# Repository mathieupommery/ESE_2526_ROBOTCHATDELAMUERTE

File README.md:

# Cat-and-Mouse Robot Project

## Table of contents
1. [Introduction](#1-introduction)
2. [FOC omniwheel](#2-foc-omniwheel)
   1. [Hardware](#21-hardware)
      1. [Electronics](#211-electronics)
      2. [Mechanics](#212-mechanics)
   2. [Software (Overview)](#22-software-overview)
   3. [Bottleneck](#23-bottleneck)
3. [DC omniwheel](#3-dc-omniwheel)
   1. [New Motor control PCB](#31-new-motor-control-pcb)
   2. [Adapting the frame to allocate new DC motors, and more...](#32-adapting-the-frame-to-allocate-new-dc-motors-and-more)
   3. [Movement strategy](#33-movement-strategy)
      1. [Cat mode](#331-cat-mode)
      2. [Mouse mode](#332-mouse-mode)
   4. [Issues](#34-issues)
4. [Regular DC](#4-regular-dc)
   1. [Hardware](#41-hardware)
5. [Strategy Implementation](#5-strategy-implementation)
   1. [Overview of Cat/Mouse Mode](#51-overview-of-cat/mouse-mode)
   2. [LiDAR handling](#52-lidar-handling)
   3. [Motor control](#53-motor-control)
   4. [Additional PIMP mode](#54-additional-pimp-mode)

## 1. Introduction
This project aims to design and build a **mobile robotic system** capable of playing a "cat and mouse" pursuit game.  
It combines **real-time embedded control**, **sensor fusion**, and **mechanical design** to create an autonomous robot capable of chasing or evading another robot in a dynamic environment. 
In addition to that we built ESP32-S3 based audio system with the intent of **listening with a mic** and answering using **AI based model through wifi connection and online server.**

## 2. FOC omniwheel

We first wanted to make a three omniwheeled robot with FOC control on brushless motors.

### 2.1. Hardware

The hardware design is divided into two main parts:

#### 2.1.1. Electronics
The electronic subsystem provides sensing, control, and communication between the robot's components. 

##### Motherboard

###### V1

**Main features:**
- **Microcontroller:** 480Mhz STM32H743 in TFBGA100 package, 1MB RAM 2MB Flash 
- **Sensors:** ADXL343 accelerometer and 3x TOF sensor 
- **Actuators:** UART COM for each STM32 FOC controller
- **Power Management:** 2.5A 5V buck, separate 3.3V ldo between mcu and accelerometer.  
- **Communication:** SPI / UART / Wireless link via esp32-C6
- **Features:** Up to 1Gb nand flash of 512Mb Nor flash 

This board work perfectly fine on it's own, we upgraded it just for adding option and better looking connector 

###### V2

This version improved the audio part by adding a micro sd card wich replaced the previous NOR flash in order to get faster read and write speed and easier data management (indeed nor flash work on 4096 byte secotr that has to be erased before program, it is harder to implement in order to deal with the usb msc protocol and slower) on top of that we moved all the **audio processing into a faster esp32-S3** wich communicates with the stm32 by a uart link, it allows us to get **real AI functionnality** by using wifi link and also communicate with the **STM32 that controls all of the Robot's movements**.  
Finally this board is designed as a two board stack with the FOC controller v2.

**Main features:**
- **Microcontroller:** 480Mhz STM32H743 in TFBGA100 package, 1MB RAM 2MB Flash 
- **Sensors:** ADXL343 accelerometer and 3x TOF sensor, ICS43434 I2S mems microphone 
- **Actuators:** UART COM for each STM32 FOC controller
- **Power Management:** 
-2.5A 5V buck with up to 30v input capability, -separate 3.3V ldo between for accelerometer
-latest 3.3v SIP buck from texas instrument for both mcu
- decoupling caps near motor connector.

- **Communication:** SPI / UART / Wireless link via esp32-s3 (bluetooth 5.0, wifi 2.4G)
- **Features:** Sd card port and esp32-s3 to manage all the audio part with class d amplifier max99357 and microphone in order to get AI to answer via a wifi call to an api. 

##### FOC STM32 based Controller

###### V1

The FOC controller is build arround a Iflight GBM2804H-100T motor, that we will use in direct drive to drive our robot using a 3 Wheel Omniwheel base. 

**Main features:**
- **Microcontroller:**  STSPIN32G0A2 built in soc with integrated STM32G031 and gate driver and opamp
- **Sensors:** MA330 absolut spi angle sensor 1uS measure time and 3us latency 
- **Features:** Uart communication to mainboard.

**encountered problem** 
This controller work very well for foc control but sensorless, indeed we the main problem is the stm32g031 itself, it don't have hardware floating point unit built in too clark and parks transform run solwer on top of that it run at only 64Mhz wich is a little slow to implement the spi communication with the MA330 on top of all calculs every 5ms.

We even tried to use only low layer librarie with prearmed dma transfer in order to cut down the cpu use in the current loop but the main problem was the lack of fpu wich even with fixed point number was hard to deal with.

In conclusion this driver is great for sensorless foc control or here for torque reason at low speed we need sensored control and we should have stepped up to the sts32ping4 but we prefer to goes in to brushed motor in order to gain time for the other problems. 

#### 2.1.2. Mechanics
The mechanical subsystem handles motion, traction, and physical interaction. 

**Main features:**
- **frame:** Lightweight 3D-printed or CNC-machined frame  
- **Drive System:** Differential or mecanum wheels for agile motion  
- **Mounts:** Sensor and board supports designed for modular assembly  
- **Simulation / CAD:** Designed on Onshape

### 2.2. Software (Overview)
While hardware is the main focus, the robot also runs control and perception algorithms:

- **Real-time tasks:** Sensor acquisition, motor control, communication  
- **Sensor fusion:** Madgwick filter for attitude estimation  
- **Behavior layer:** Cat-and-mouse logic (chase / evade modes)  
- **Debug tools:** UART logs, LED indicators, optional telemetry GUI  

### 2.3. Bottleneck

However the STM32G0 are too slow for proper sensored FOC control, even after switching to low level functions, so we had to abandon using brushless motors and switch to DC ones instead to ensure that we will be able to drive the robot. 

## 3. DC omniwheel

### 3.1. New Motor control PCB

We kept the V2 Mainboard but had to drop the idea of a V2 FOC motor control board and instead use a single STSPING4 STM32 to send the PWM to the DC motor drivers.

### 3.2. Adapting the frame to allocate new DC motors, and more... 

https://github.com/user-attachments/assets/3e3c2521-501a-48cf-ad38-90644dd84529

We changed the motor mounts to accomodate the motors under the PCB stack. We therefore had to abandon the hand holding the LiDAT aesthetic to compensate for the extra space occupied byt the PCB and Motor assembly.

Nevertheless, we managed to maintain a fun look by adding a mascott Labubu holder and led strips.

### 3.3. Movement strategy

#### 3.3.1. Cat mode

The robot would behave like a "heat seeking missile" meaning that it would target the ennemy robot, thanks to a lidar filtering and clusteriwation algorithm, and move towards it while adjusting it's orientation so that the ennemy robot stays in the directional axis of the movement bearing:  

Of course the robot being three way symmetrical it would choose it's bearing axis according to the ennemy's potition so that the closest bearing gets chosen as the "front" to minimize turning time.

Table edge detection halts the robot's movement and waits for a new target (should not happen thanks to very selective filtering)

#### 3.3.2. Mouse mode

The robot would pivot in such a way that the ennemy robot is aligned with the 180 degree LiDAR bearing and maintain a distance of at least 50cm.  

Table edge is handled by "reflecting" the robot to the  largest mid-angle between the table's edge line and the approaching ennemy's relative position, much like the "bouncing DVD logo".

### 3.4. Issues

Everything was advancing relatively smoothly the PCBs were promptly assembled and tested. Despite our attention to detail we could not have anticipated the mechanical issues that would arise from the use of low temperature bismuth based soldering paste.
The solder points were not mechanically sound leading to smd connectors breaking off and even bridging in between the USART and the Power connection underneath the connector during reheating while adjusting the solder points.  This unfortunately led to the loss of several STM32H7 chips delaying our work while we searched for the issue cqused by the auxiliary PCB, whereas our assumptions were, in order of testing:
- STM32H7 BGA pads bridging
- Mainboard connector bridging
- Motor board connector bridging

Thus leading to the loss of several pricey components.

Furthermore after some time one of the encoders from the DC motors stopped working. We had to spend some precious time to try and locate the issue, resoldering components, cswapping connectors, swapping motors, debugging code. To this day the issue has not been identified with certitude, however we suspect a manufacturing issue that led to a delamination on the single, non redundant, via transmitting the encoder logic... another issue wich could not have been anticipated.

With the short time we had left we decided that assembling a new board was not ideal, especially with the fast approaching holidays and final exams, all the more if we factor in the potential breaking points of the assembly process (mechanically and thermally fragile connectors leading to the use of sub-optimal bismuth solderpaste, potential unforeseen PCB manufacturing issues). Thus, we opted for a complete mechanical redesign to avoid further time consuming and error inducing PCB assembly, moving from a three wheeled robot to a simple two wheeled robot.

## 4. Regular DC

It is with great regeret and disappointment that we opted for the failsafe route: basic geometry, relying on the leftover functionalities of our already assembled PCBs.

### 4.1. Hardware

Here is the final aesthetic of the robot, granted, this version is much less elegant and complex, but that is it's vantage point, its simplicity has allowed us to obtain a functional result, after exploring many challenging and most educational approaches. 

## 5. Strategy Implementation

### 5.1 Overview of Cat/Mouse Mode

In cat mode the robot acts like a heat seeking missile, meaning that when the Lidar detects an object the robot orients itself so that the object sits at a 180° bearing on the Lidar reading, meaning that the object is directly in front of the robot. When a 5° orientation precision is reached the robot moves forward and only stops to reorient itself if the orientation error becomes greater than 5°.

In mouse mode we adopt a pseudo-random flee method. The robot orients itself so that the cat sits behind it and moves forward when the difference in distance becomes lower than 50cm. If the side of a table is met the robot reorients itself to face the greatest half of the angle formed between the table's border and the cat's bearing position, thus always fleeing where there is more space.

### 5.2 LiDAR handling

The LiDAR is spun at roughly 8Hz guaranteeing a 1° accuracy and fast response. After parsing the RX data is stored in a 360 uiint32 long list, each index increment analog to a 1° increment, only the points ranging from 0 to 3m are stored. Then a clusterization algorithm detects and filters the objects of diameter greater than 3cm and smaller than 8cm, which could be the opposing robot's LiDAR. Then the detected clusters are classified according to their computed size in order to isolate the most likely candidate to be the ennemy's LiDAR.

### 5.3 Motor control

Two PCBs are mounted, the top one is equipped with the STM32H7 and ESP32S3 for great computing capabilities and handling Wifi and Buetooth connectivity as well as aesthetic equipments such as LEDs, Screens and Speakers. The STM32H7 communicates the movement commands to the STM32G4 mounted on the bottom PCB at a 200Hz frequency, and the bottom PCB handles the motor control PIDs and returns the speeds for the STM32H7 to compute the odometry.

### 5.4 Additional PIMP mode

In an attempt to spice things up we experimented with the cinematics of a two omniwheeled robot, more particularly its ability to drift by taking advantage of the lateral movement allowed by the rollers. Hence by advancing and turning simultaneously it is possible to crab walkj in a circle. Hence a third state that although not as elegant as a computed evasion from the cat could be used to run fast circles around the cat when in mouse mode.

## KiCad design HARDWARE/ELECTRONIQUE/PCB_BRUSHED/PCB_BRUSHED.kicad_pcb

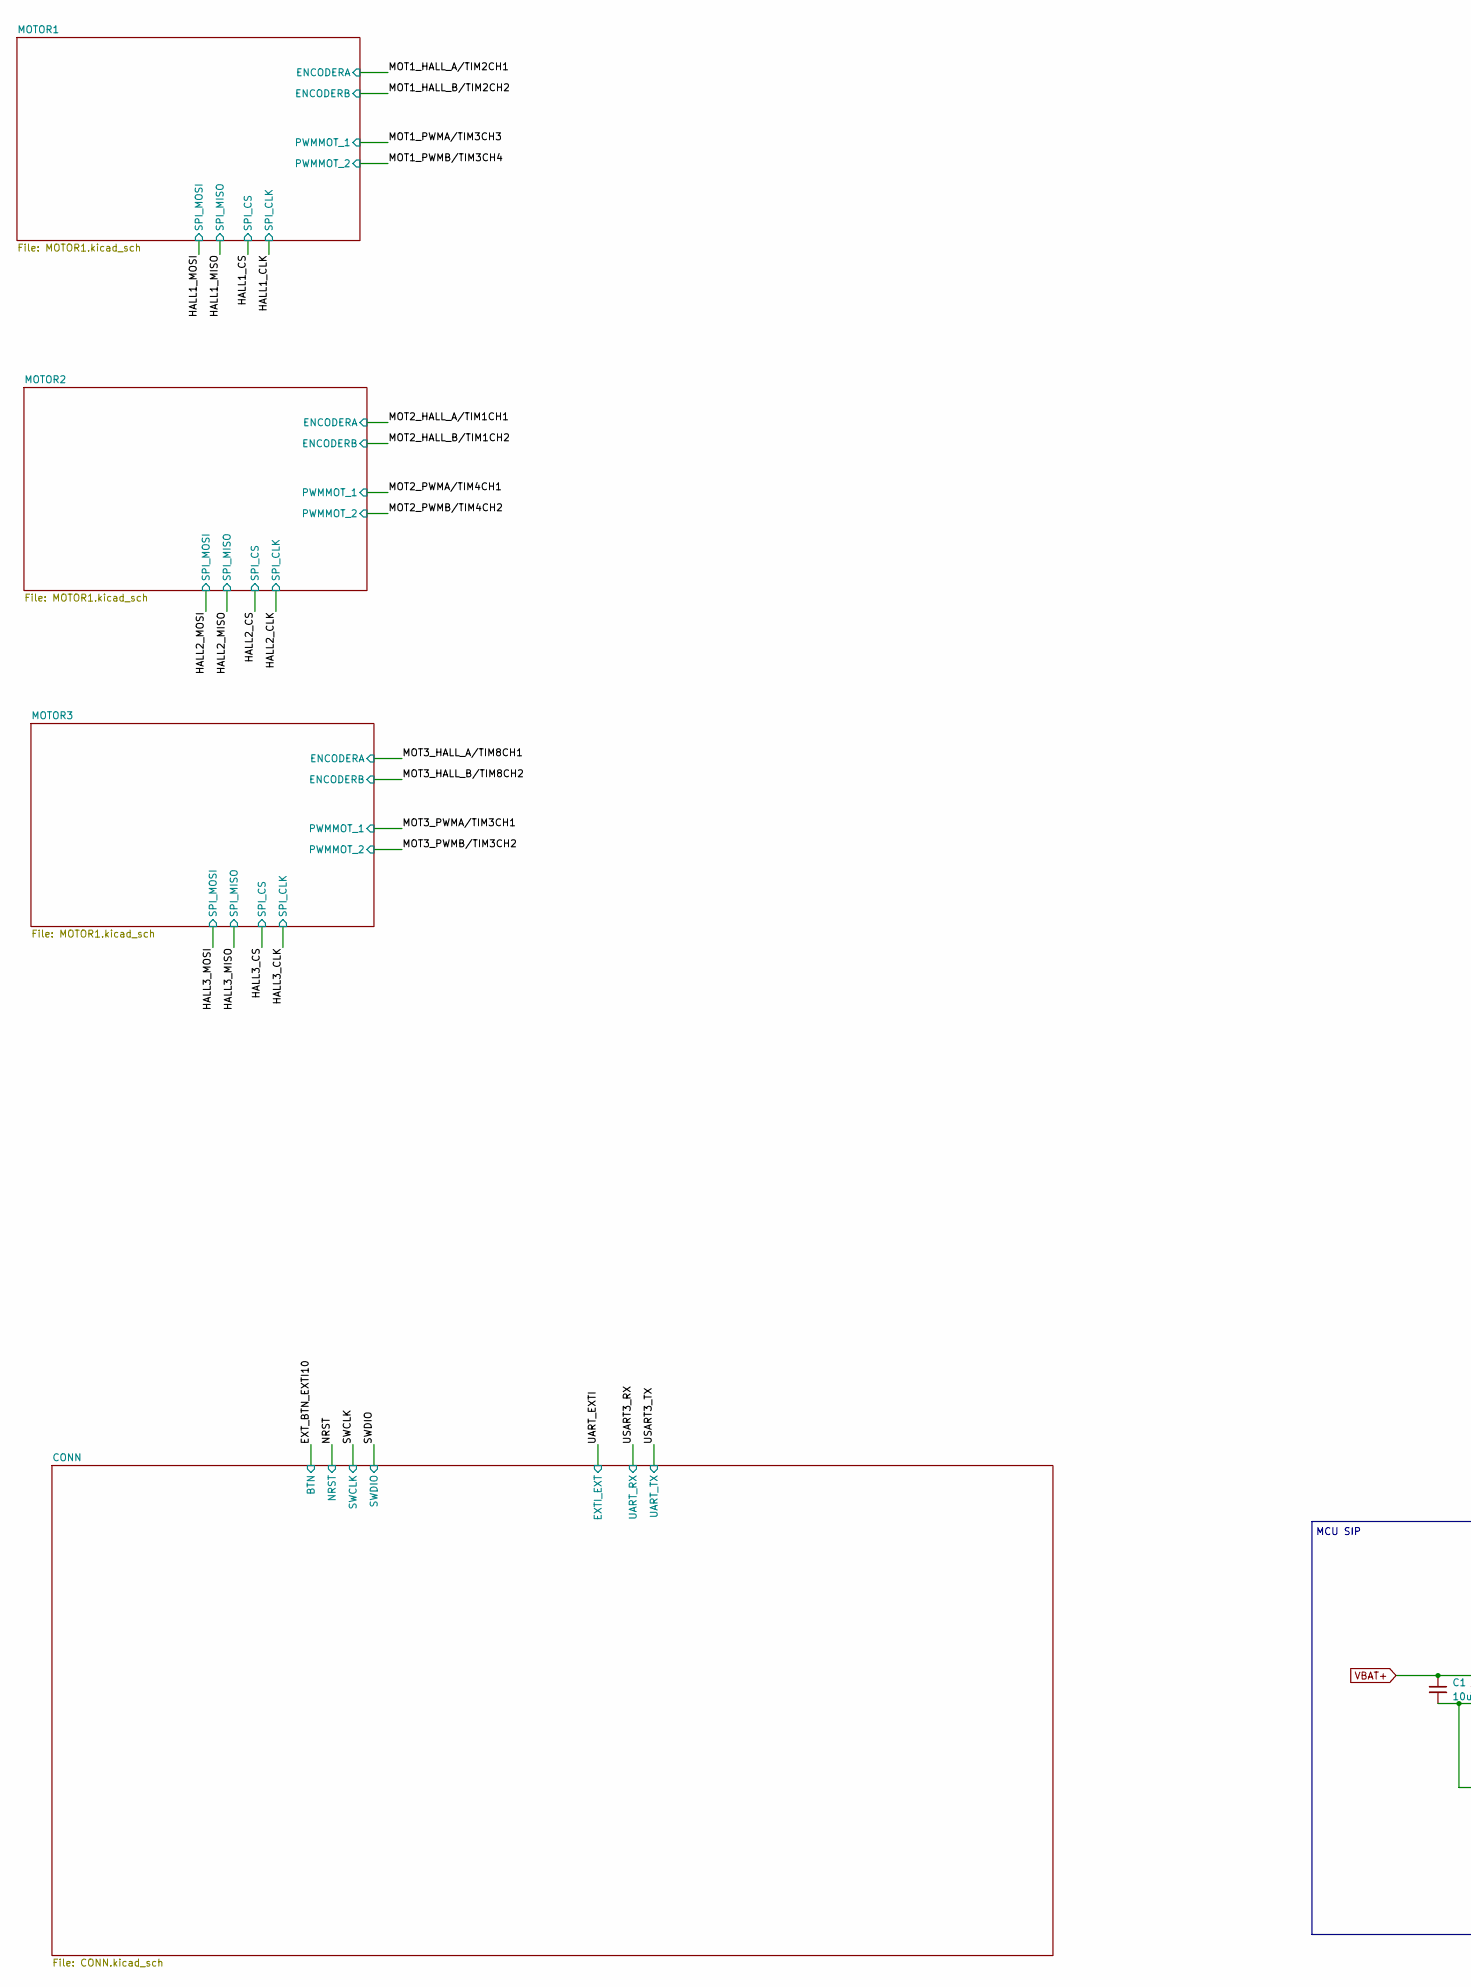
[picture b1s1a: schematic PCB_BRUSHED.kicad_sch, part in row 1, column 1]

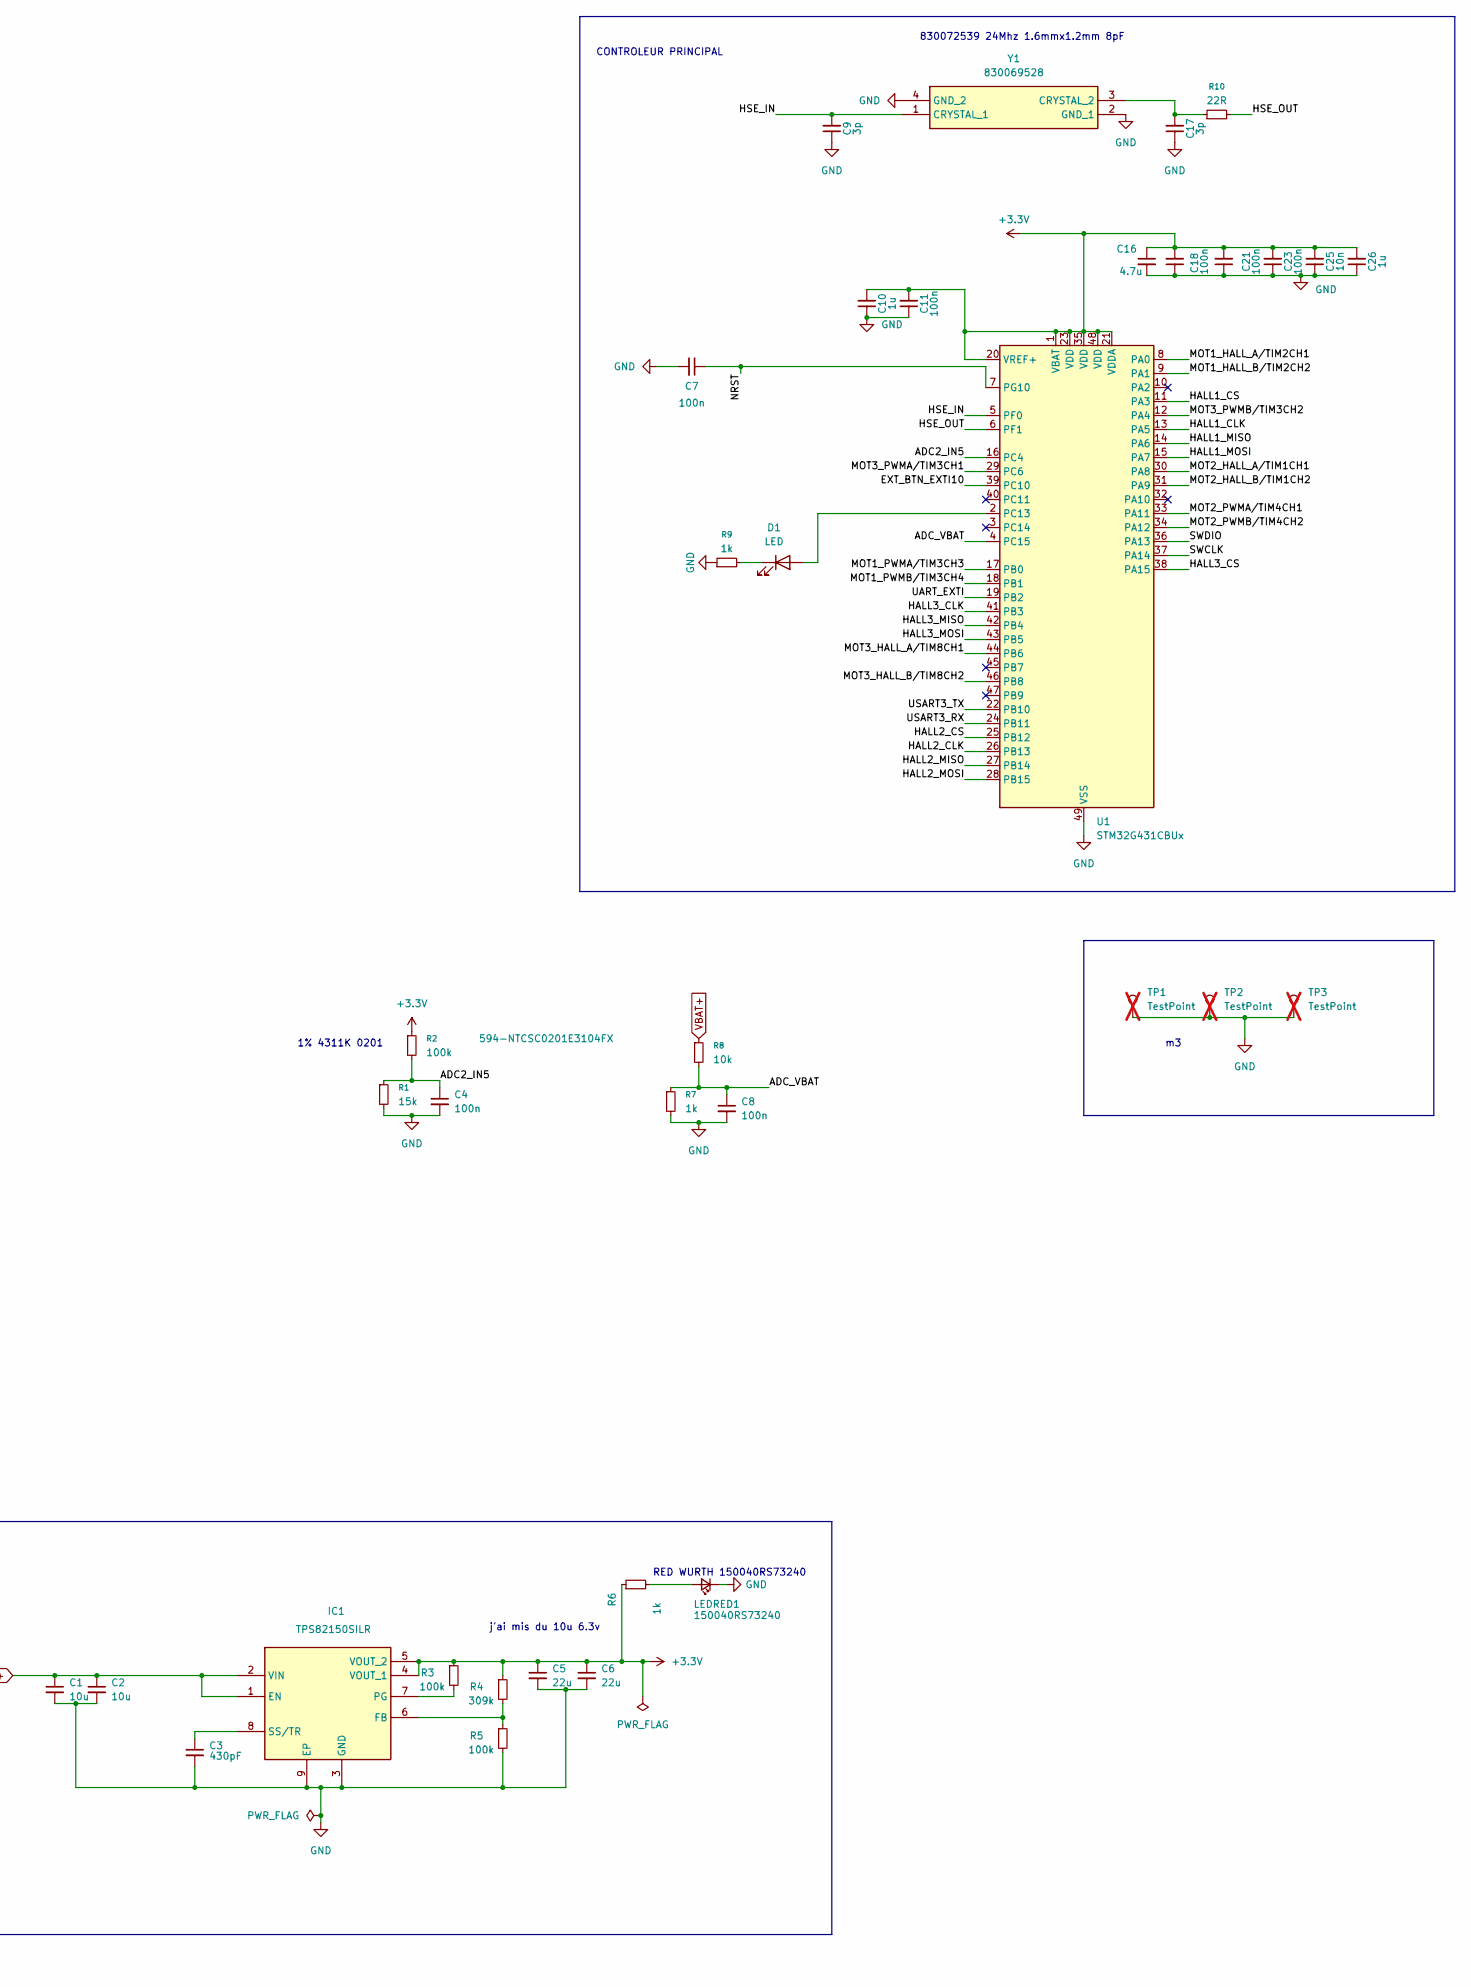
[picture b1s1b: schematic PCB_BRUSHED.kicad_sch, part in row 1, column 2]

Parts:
C1, C2: 10u; C_0603_1608Metric; Manufacturer_Part_Number 885012105012; Mouser Part Number 710-885012105012
C3: 430pF; C_0201_0603Metric_Pad0.64x0.40mm_HandSolder
C4, C7, C8, C11, C18, C21, C23: 100n; C_0201_0603Metric_Pad0.64x0.40mm_HandSolder
C5, C6: 22u; C_0603_1608Metric; Manufacturer_Part_Number 885012105012; Mouser Part Number 710-885012105012
C9, C17: 3p; C_0201_0603Metric_Pad0.64x0.40mm_HandSolder
C10, C26: 1u; C_0402_1005Metric_Pad0.74x0.62mm_HandSolder
C16: 4.7u; C_0402_1005Metric_Pad0.74x0.62mm_HandSolder
C25: 10n; C_0201_0603Metric_Pad0.64x0.40mm_HandSolder
D1: LED; LED_0402_1005Metric
IC1: TPS82150SILR; TPS82130SILT; Manufacturer_Part_Number TPS82150SILR; Mouser Part Number 595-TPS82150SILR
LEDRED1: 150040RS73240; LED_0402_1005Metric; Manufacturer_Part_Number 150040RS73240; Mouser Part Number 710-150040RS73240
R1: 15k; R_0201_0603Metric_Pad0.64x0.40mm_HandSolder
R2: 100k; R_0201_0603Metric_Pad0.64x0.40mm_HandSolder; Manufacturer_Part_Number NTCSC0201E3104FX; Mouser Part Number 594-NTCSC0201E3104FX
R3, R5: 100k; R_0201_0603Metric_Pad0.64x0.40mm_HandSolder
R4: 309k; R_0201_0603Metric_Pad0.64x0.40mm_HandSolder
R6: 1k; R_0201_0603Metric_Pad0.64x0.40mm_HandSolder; Manufacturer_Part_Number ERJ-1GNF1001C; Mouser Part Number 667-ERJ-1GNF1001C
R7, R9: 1k; R_0201_0603Metric_Pad0.64x0.40mm_HandSolder
R8: 10k; R_0201_0603Metric_Pad0.64x0.40mm_HandSolder
R10: 22R; R_0201_0603Metric_Pad0.64x0.40mm_HandSolder
TP1, TP2, TP3: TestPoint; MountingHole_2.5mm_Pad_Via; not fitted
U1: STM32G431CBUx; QFN-48-1EP_7x7mm_P0.5mm_EP5.6x5.6mm
Y1: 830069528; Manufacturer_Part_Number 830069528; Mouser Part Number 710-830069528

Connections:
+3.3V: C5.1, C6.1, C10.2, C11.2, C16.1, C18.2, C21.2, C23.2, C25.2, C26.2, IC1.4 (VOUT_1), IC1.5 (VOUT_2), R2.1, R3.1, R4.1, R6.1, U1.1 (VBAT), U1.20 (VREF+), U1.21 (VDDA), U1.23 (VDD), U1.35 (VDD), U1.48 (VDD); also elsewhere on the board
/ADC2_IN5: C4.1, R1.1, R2.2, U1.16 (PC4)
/ADC_VBAT: C8.1, R7.1, R8.2, U1.4 (PC15)
/EXT_BTN_EXTI10: U1.39 (PC10); also elsewhere on the board
/HALL1_CLK: U1.13 (PA5); also elsewhere on the board
/HALL1_CS: U1.11 (PA3); also elsewhere on the board
/HALL1_MISO: U1.14 (PA6); also elsewhere on the board
/HALL1_MOSI: U1.15 (PA7); also elsewhere on the board
/HALL2_CLK: U1.26 (PB13); also elsewhere on the board
/HALL2_CS: U1.25 (PB12); also elsewhere on the board
/HALL2_MISO: U1.27 (PB14); also elsewhere on the board
/HALL2_MOSI: U1.28 (PB15); also elsewhere on the board
/HALL3_CLK: U1.41 (PB3); also elsewhere on the board
/HALL3_CS: U1.38 (PA15); also elsewhere on the board
/HALL3_MISO: U1.42 (PB4); also elsewhere on the board
/HALL3_MOSI: U1.43 (PB5); also elsewhere on the board
/HSE_IN: C9.2, U1.5 (PF0), Y1.1 (CRYSTAL_1)
/HSE_OUT: R10.2, U1.6 (PF1)
/MOT1_HALL_A/TIM2CH1: U1.8 (PA0); also elsewhere on the board
/MOT1_HALL_B/TIM2CH2: U1.9 (PA1); also elsewhere on the board
/MOT1_PWMA/TIM3CH3: U1.17 (PB0); also elsewhere on the board
/MOT1_PWMB/TIM3CH4: U1.18 (PB1); also elsewhere on the board
/MOT2_HALL_A/TIM1CH1: U1.30 (PA8); also elsewhere on the board
/MOT2_HALL_B/TIM1CH2: U1.31 (PA9); also elsewhere on the board
/MOT2_PWMA/TIM4CH1: U1.33 (PA11); also elsewhere on the board
/MOT2_PWMB/TIM4CH2: U1.34 (PA12); also elsewhere on the board
/MOT3_HALL_A/TIM8CH1: U1.44 (PB6); also elsewhere on the board
/MOT3_HALL_B/TIM8CH2: U1.46 (PB8); also elsewhere on the board
/MOT3_PWMA/TIM3CH1: U1.29 (PC6); also elsewhere on the board
/MOT3_PWMB/TIM3CH2: U1.12 (PA4); also elsewhere on the board
/NRST: C7.1, U1.7 (PG10); also elsewhere on the board
/SWCLK: U1.37 (PA14); also elsewhere on the board
/SWDIO: U1.36 (PA13); also elsewhere on the board
/UART_EXTI: U1.19 (PB2); also elsewhere on the board
/USART3_RX: U1.24 (PB11); also elsewhere on the board
/USART3_TX: U1.22 (PB10); also elsewhere on the board
GND: C1.2, C2.2, C3.2, C4.2, C5.2, C6.2, C7.2, C8.2, C9.1, C10.1, C11.1, C16.2, C17.1, C18.1, C21.1, C23.1, C25.1, C26.1, IC1.3 (GND), IC1.9 (EP), LEDRED1.1 (K), R1.2, R5.2, R7.2, R9.1, TP1.1, TP2.1, TP3.1, U1.49 (VSS), Y1.2 (GND_1), Y1.4 (GND_2); also elsewhere on the board
unnamed: D1.2 (A), U1.2 (PC13)
unnamed: D1.1 (K), R9.2
unnamed: IC1.6 (FB), R4.2, R5.1
unnamed: IC1.7 (PG), R3.2
unnamed: C3.1, IC1.8 (SS/TR)
unnamed: LEDRED1.2 (A), R6.2
unnamed: C17.2, R10.1, Y1.3 (CRYSTAL_2)
VBAT+: C1.1, C2.1, IC1.1 (EN), IC1.2 (VIN), R8.1; also elsewhere on the board

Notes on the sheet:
RED WURTH 150040RS73240
1% 4311K 0201
830072539 24Mhz 1.6mmx1.2mm 8pF
j'ai mis du 10u 6.3v
MCU SIP
CONTROLEUR PRINCIPAL

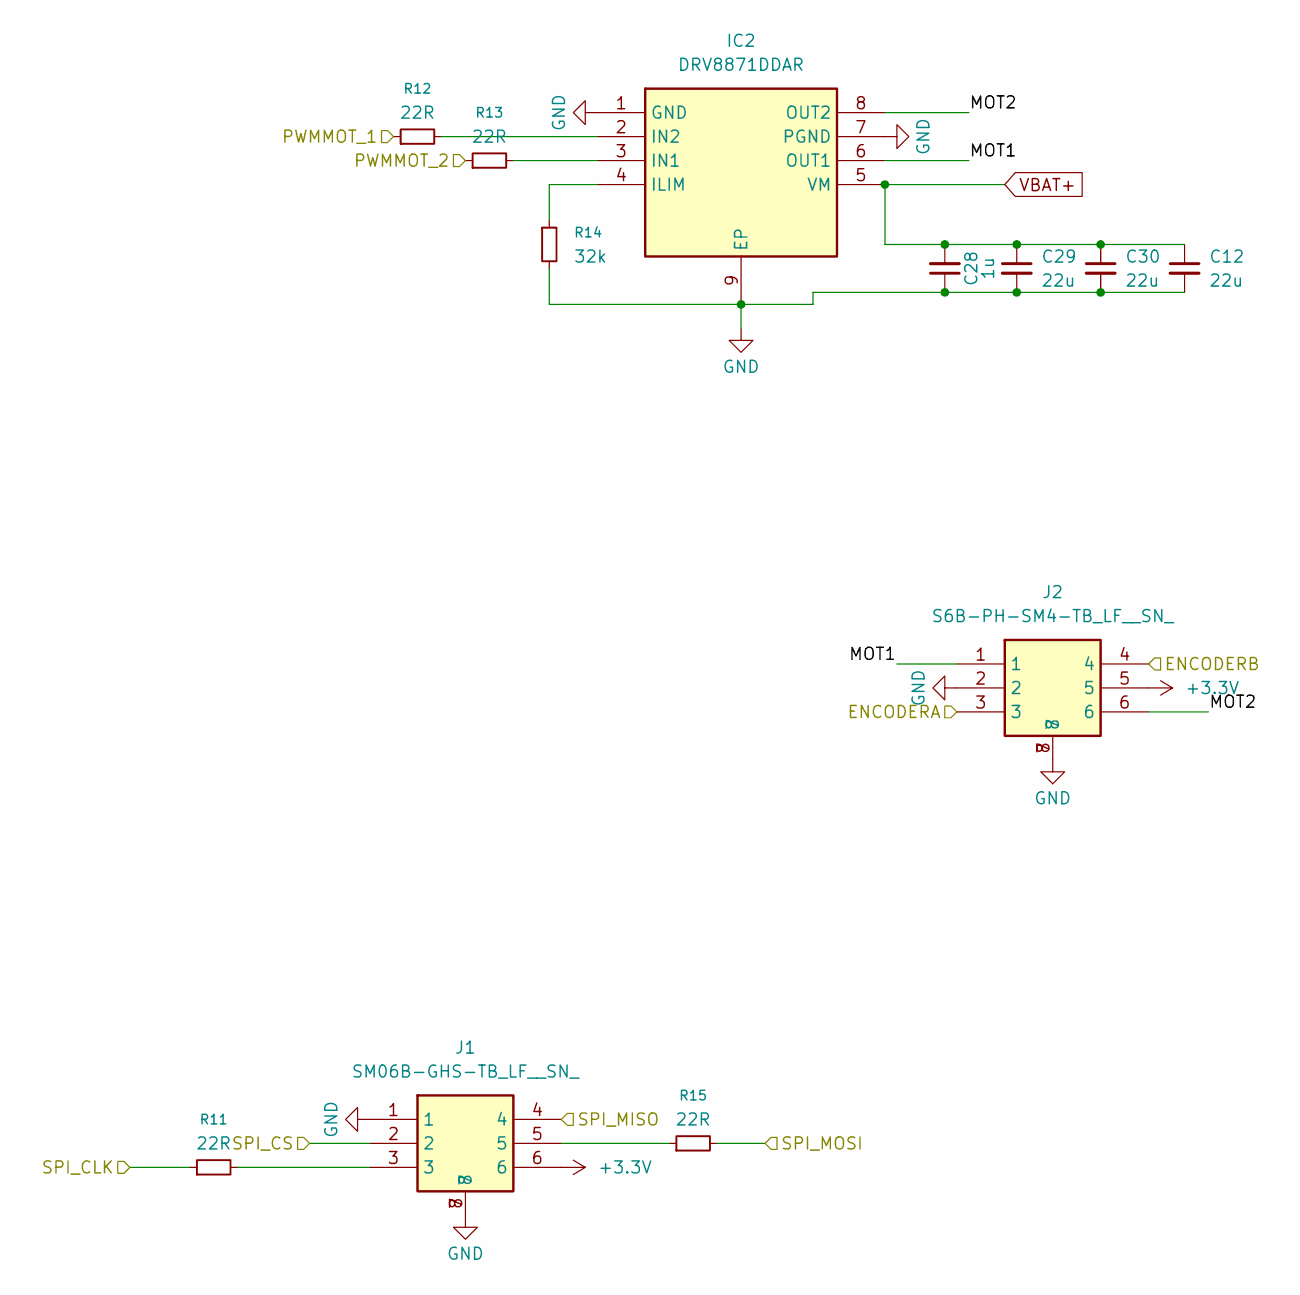
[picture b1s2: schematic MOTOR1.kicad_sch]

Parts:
C12, C29, C30: 22u; C_0805_2012Metric; Manufacturer_Part_Number GRM21BR61E226ME4L; Mouser Part Number 81-GRM21BR61E226ME4L
C28: 1u; C_0402_1005Metric_Pad0.74x0.62mm_HandSolder
IC2: DRV8871DDAR; SOIC127P600X170-9N; Manufacturer_Part_Number DRV8871DDAR; Mouser Part Number 595-DRV8871DDAR
J1: SM06B-GHS-TB_LF__SN_; SM06B-GHS-TB; Manufacturer_Part_Number SM06B-GHS-TB(LF)(SN); Mouser Part Number N/A
J2: S6B-PH-SM4-TB_LF__SN_; S6B-PH-SM4-TB_LF__SN__3; Manufacturer_Part_Number S6B-PH-SM4-TB(LF)(SN); Mouser Part Number N/A
R11, R12, R13, R15: 22R; R_0201_0603Metric_Pad0.64x0.40mm_HandSolder
R14: 32k; R_0201_0603Metric_Pad0.64x0.40mm_HandSolder

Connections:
+3.3V: J1.6, J2.5; also elsewhere on the board
/HALL2_CLK: R11.1; also elsewhere on the board
/HALL2_CS: J1.2; also elsewhere on the board
/HALL2_MISO: J1.4; also elsewhere on the board
/HALL2_MOSI: R15.2; also elsewhere on the board
/MOT2_HALL_A/TIM1CH1: J2.3; also elsewhere on the board
/MOT2_HALL_B/TIM1CH2: J2.4; also elsewhere on the board
/MOT2_PWMA/TIM4CH1: R12.1; also elsewhere on the board
/MOT2_PWMB/TIM4CH2: R13.1; also elsewhere on the board
/MOTOR2/MOT1: IC2.6 (OUT1), J2.1
/MOTOR2/MOT2: IC2.8 (OUT2), J2.6
GND: C12.2, C28.1, C29.2, C30.2, IC2.1 (GND), IC2.7 (PGND), IC2.9 (EP), J1.1, J1.7, J1.8, J2.2, J2.7, J2.8, R14.2; also elsewhere on the board
unnamed: IC2.4 (ILIM), R14.1
unnamed: IC2.3 (IN1), R13.2
unnamed: IC2.2 (IN2), R12.2
unnamed: J1.3, R11.2
unnamed: J1.5, R15.1
VBAT+: C12.1, C28.2, C29.1, C30.1, IC2.5 (VM); also elsewhere on the board

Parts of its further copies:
C13, C14, C32, C33, C36, C37: 22u; C_0805_2012Metric; Manufacturer_Part_Number GRM21BR61E226ME4L; Mouser Part Number 81-GRM21BR61E226ME4L
C31, C35: 1u; C_0402_1005Metric_Pad0.74x0.62mm_HandSolder
IC3, IC4: DRV8871DDAR; SOIC127P600X170-9N; Manufacturer_Part_Number DRV8871DDAR; Mouser Part Number 595-DRV8871DDAR
J3, J9: SM06B-GHS-TB_LF__SN_; SM06B-GHS-TB; Manufacturer_Part_Number SM06B-GHS-TB(LF)(SN); Mouser Part Number N/A
J4, J10: S6B-PH-SM4-TB_LF__SN_; S6B-PH-SM4-TB_LF__SN__3; Manufacturer_Part_Number S6B-PH-SM4-TB(LF)(SN); Mouser Part Number N/A
R16, R17, R18, R20, R22, R23, R24, R26: 22R; R_0201_0603Metric_Pad0.64x0.40mm_HandSolder
R19, R25: 32k; R_0201_0603Metric_Pad0.64x0.40mm_HandSolder

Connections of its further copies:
+3.3V: J3.6, J4.5, J9.6, J10.5; also elsewhere on the board
/HALL1_CLK: R16.1; also elsewhere on the board
/HALL1_CS: J3.2; also elsewhere on the board
/HALL1_MISO: J3.4; also elsewhere on the board
/HALL1_MOSI: R20.2; also elsewhere on the board
/HALL3_CLK: R22.1; also elsewhere on the board
/HALL3_CS: J9.2; also elsewhere on the board
/HALL3_MISO: J9.4; also elsewhere on the board
/HALL3_MOSI: R26.2; also elsewhere on the board
/MOT1_HALL_A/TIM2CH1: J4.3; also elsewhere on the board
/MOT1_HALL_B/TIM2CH2: J4.4; also elsewhere on the board
/MOT1_PWMA/TIM3CH3: R17.1; also elsewhere on the board
/MOT1_PWMB/TIM3CH4: R18.1; also elsewhere on the board
/MOT3_HALL_A/TIM8CH1: J10.3; also elsewhere on the board
/MOT3_HALL_B/TIM8CH2: J10.4; also elsewhere on the board
/MOT3_PWMA/TIM3CH1: R23.1; also elsewhere on the board
/MOT3_PWMB/TIM3CH2: R24.1; also elsewhere on the board
/MOTOR1/MOT1: IC3.6 (OUT1), J4.1
/MOTOR1/MOT2: IC3.8 (OUT2), J4.6
/MOTOR3/MOT1: IC4.6 (OUT1), J10.1
/MOTOR3/MOT2: IC4.8 (OUT2), J10.6
GND: C13.2, C14.2, C31.1, C32.2, C33.2, C35.1, C36.2, C37.2, IC3.1 (GND), IC3.7 (PGND), IC3.9 (EP), IC4.1 (GND), IC4.7 (PGND), IC4.9 (EP), J3.1, J3.7, J3.8, J4.2, J4.7, J4.8, J9.1, J9.7, J9.8, J10.2, J10.7, J10.8, R19.2, R25.2; also elsewhere on the board
unnamed: IC3.4 (ILIM), R19.1
unnamed: IC3.3 (IN1), R18.2
unnamed: IC3.2 (IN2), R17.2
unnamed: IC4.4 (ILIM), R25.1
unnamed: IC4.3 (IN1), R24.2
unnamed: IC4.2 (IN2), R23.2
unnamed: J3.3, R16.2
unnamed: J3.5, R20.1
unnamed: J9.3, R22.2
unnamed: J9.5, R26.1
VBAT+: C13.1, C14.1, C31.2, C32.1, C33.1, C35.2, C36.1, C37.1, IC3.5 (VM), IC4.5 (VM); also elsewhere on the board

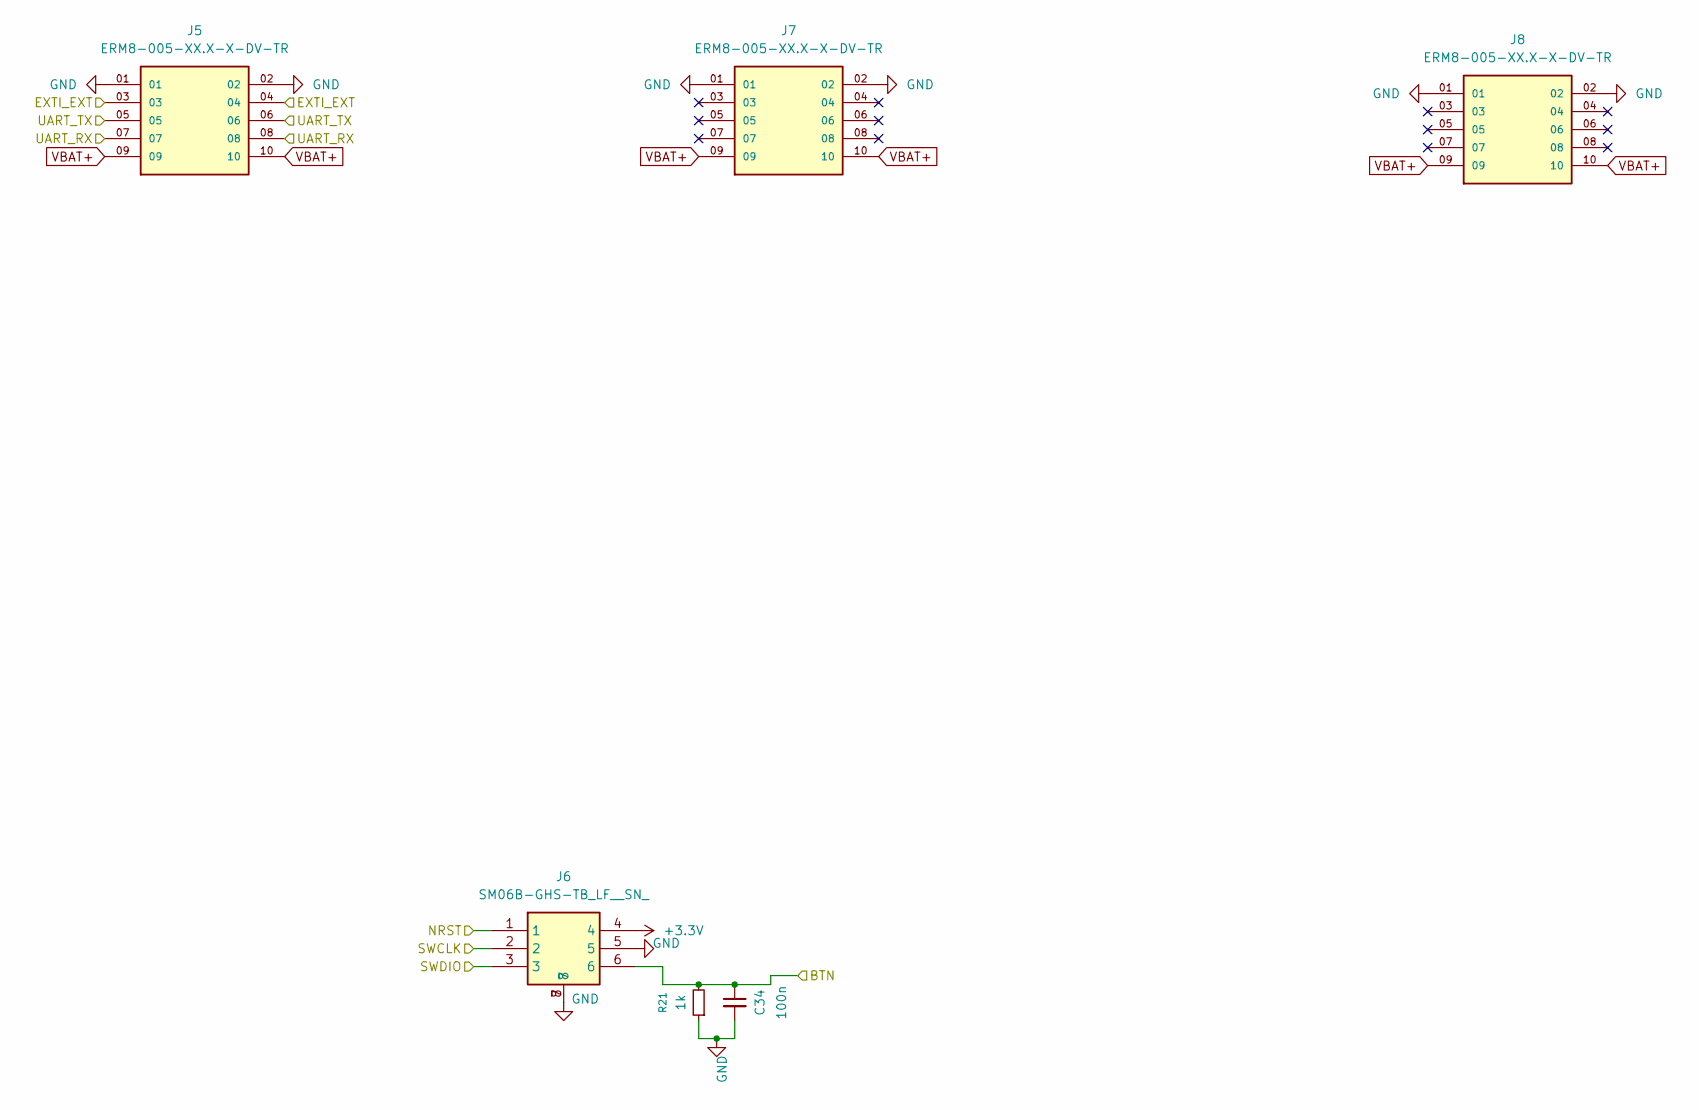
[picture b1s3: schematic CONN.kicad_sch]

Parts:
C34: 100n; C_0201_0603Metric_Pad0.64x0.40mm_HandSolder
J5, J7, J8: ERM8-005-XX.X-X-DV-TR; SAMTEC_ERM8-005-XX.X-X-DV-TR; PARTREV L
J6: SM06B-GHS-TB_LF__SN_; SM06B-GHS-TB; Manufacturer_Part_Number SM06B-GHS-TB(LF)(SN); Mouser Part Number N/A
R21: 1k; R_0201_0603Metric_Pad0.64x0.40mm_HandSolder

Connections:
+3.3V: J6.4; also elsewhere on the board
/EXT_BTN_EXTI10: C34.1, J6.6, R21.2; also elsewhere on the board
/NRST: J6.1; also elsewhere on the board
/SWCLK: J6.2; also elsewhere on the board
/SWDIO: J6.3; also elsewhere on the board
/UART_EXTI: J5.03, J5.04; also elsewhere on the board
/USART3_RX: J5.07, J5.08; also elsewhere on the board
/USART3_TX: J5.05, J5.06; also elsewhere on the board
GND: C34.2, J5.01, J5.02, J6.5, J6.7, J6.8, J7.01, J7.02, J8.01, J8.02, R21.1; also elsewhere on the board
VBAT+: J5.09, J5.10, J7.09, J7.10, J8.09, J8.10; also elsewhere on the board

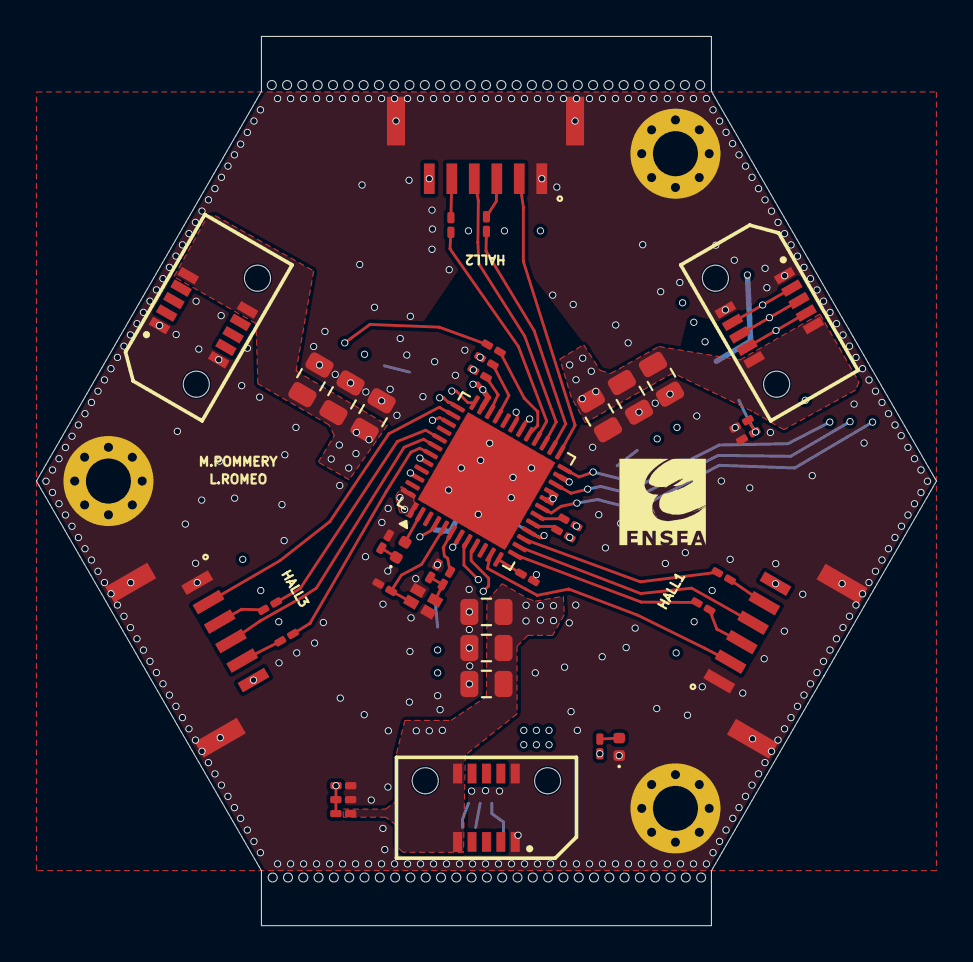
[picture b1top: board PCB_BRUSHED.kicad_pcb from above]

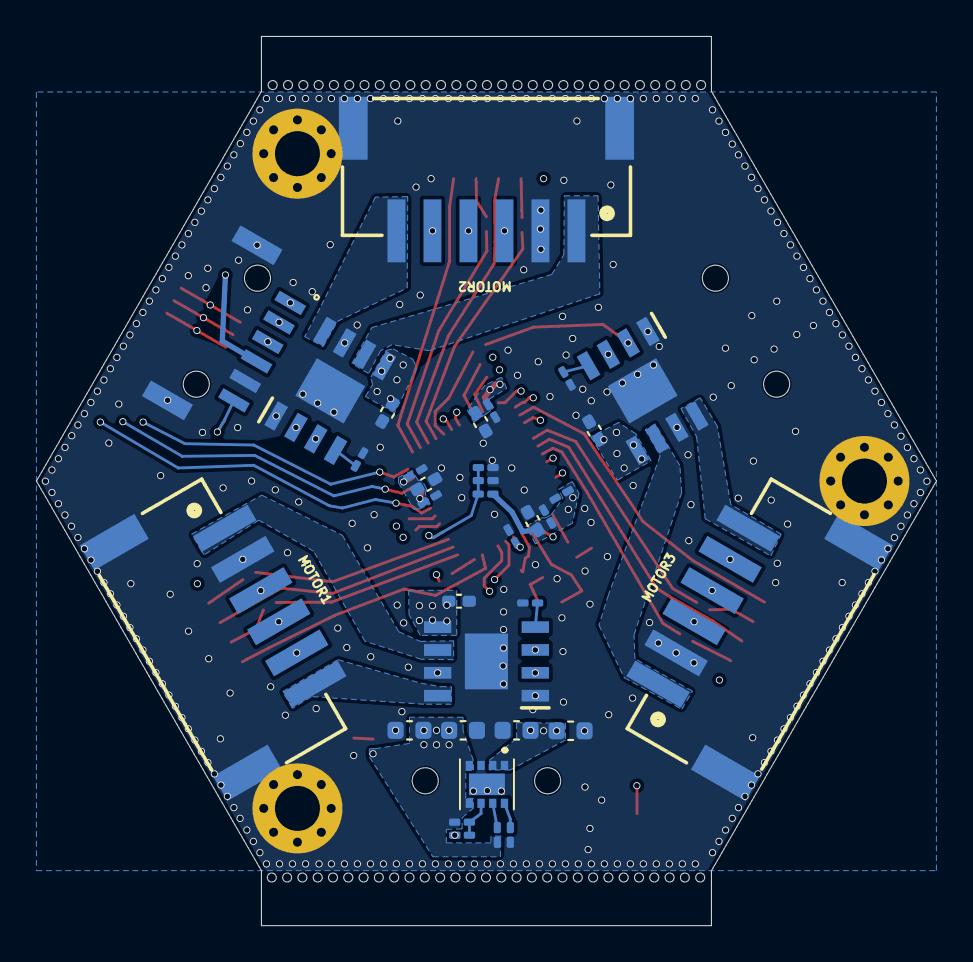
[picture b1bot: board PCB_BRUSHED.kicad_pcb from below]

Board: 6 copper layers, 50.0 x 49.4 mm, 78 parts (34 on the bottom side), 66 nets.
